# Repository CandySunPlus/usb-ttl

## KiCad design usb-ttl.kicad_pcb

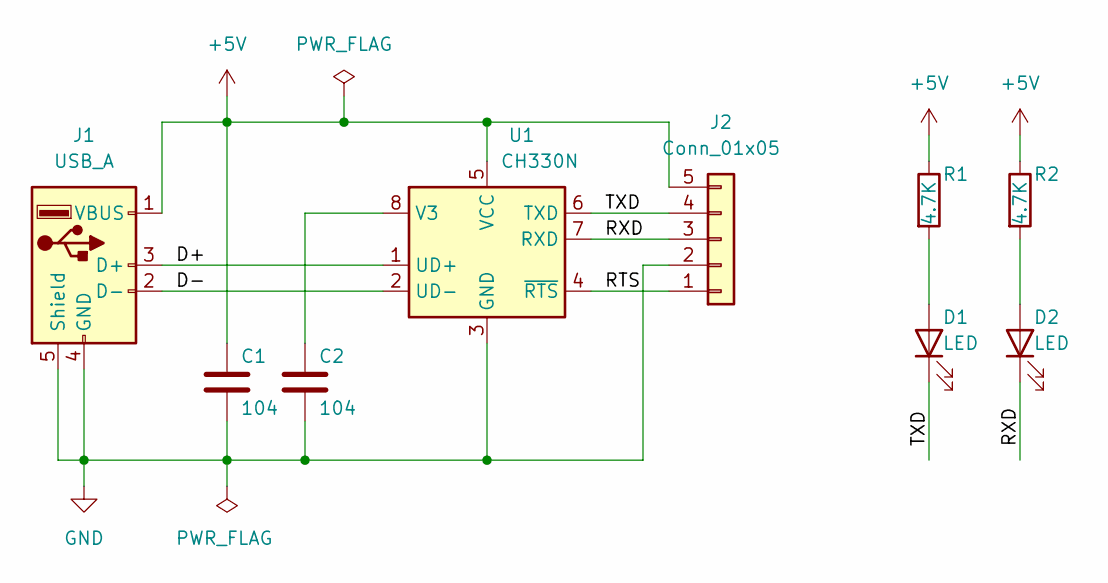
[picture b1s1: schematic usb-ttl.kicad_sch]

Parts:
C1, C2: 104
D1: LED
D2: LED; LED_0603_1608Metric
J1: USB_A
J2: Conn_01x05
R1: 4.7K
R2: 4.7K; R_0603_1608Metric
U1: CH330N

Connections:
+5V: C1.1, J1.1 (VBUS), J2.5, R1.1, R2.1, U1.5 (VCC)
/D+: J1.3 (D+), U1.1 (UD+)
/D-: J1.2 (D-), U1.2 (UD-)
/RTS: J2.1, U1.4 (~RTS)
/RXD: D2.1 (K), J2.3, U1.7 (RXD)
/TXD: D1.1 (K), J2.4, U1.6 (TXD)
GND: C1.2, C2.2, J1.4 (GND), J1.5 (Shield), J2.2, U1.3 (GND)
unnamed: C2.1, U1.8 (V3)
unnamed: D1.2 (A), R1.2
unnamed: D2.2 (A), R2.2

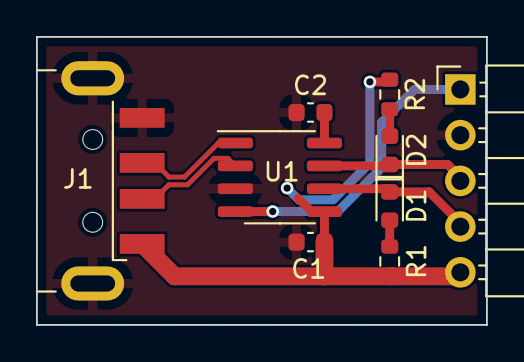
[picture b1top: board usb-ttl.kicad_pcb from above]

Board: 2 copper layers, 25.0 x 16.0 mm, 9 parts (0 on the bottom side), 10 nets.

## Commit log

2022-04-26 first updated
